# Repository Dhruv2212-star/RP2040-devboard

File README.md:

# RP2040 based devboard. 
**why did i make this board??**  
hmmmm.. well one day i realised that i have made many projects wit devboard but i have never made my own devboard.  
this was it! so this was a golden project opportunity for me to challenge myself to make something.  
i went and search some tutorials on how devboards worked and how to make them.  
Out of all of the possible devboards out there. one particular board caught my eye, it was the **RP2040** Devboard because it was reallllyy easy to make and really functional and powerful because of it's storage capacity and the no. of GPIO pins it had.  

**Now let me explain to you how i built this devboard :)**  
for a Devboard to work you need to have the basic idea of the chip architecture, with our *RP2040* chip, it uses 3.3v for the main power pins but uses 1.1v for the logic pins and fortunately for our chip it has a built in voltage control which reduces the voltage to 1.1v so no need of extra components  

**decoupling capacitors**- we are using 100nF capacitors per each power pin (IOVDD) and 1uF capacitors for VREG_IN and VREG_OUT each and 2 100nF capacitors for DVDD pin, 100nF capacitor for ADC_AVDD and 100nF for USB VDD  

**Flash storage-** for storing our code in the devboard we are using W25Q128JVS chip for this function, we are going to use QSPI pins for this connection  

**Crystal oscillator**- for this build the data sheet recommends 12Mhz crystal, and in our board we are using   
ABLS-12.000MHZ-B4-T for this  

**GPIO pin extensions**- using 1x20 connectors, we extend it to connectors where we can utilize them.  

# BOM ( Bill of materials)  
## Bill of Materials (BOM)

| Reference          | Qty | Value / Part                | Footprint                               | Purchase                                      |
| ------------------ | --: | --------------------------- | --------------------------------------- | --------------------------------------------- |
| C1, C2             |   2 | 10 µF                       | `C_0603_1608Metric`                     | [Link](https://amzn.in/d/0bsal2JG)            |
| C3, C4, C5, C9–C15 |  10 | 100 nF                      | `C_0402_1005Metric`                     | [Link](https://amzn.in/d/0h4zQ3Lf)            |
| C6, C7             |   2 | 1 µF                        | `C_0402_1005Metric`                     | [Link](https://amzn.in/d/0exjZiSL)            |
| C8                 |   1 | 100 nF                      | `C_0402_1005Metric`                     | [Link](https://amzn.in/d/0hHEodPN)            |
| C16, C17           |   2 | 27 pF                       | `C_0402_1005Metric`                     | [Link](https://amzn.in/d/0bekUa1Y)            |
| D1                 |   1 | LED                         | `LED_0603_1608Metric`                   | [Link](https://amzn.in/d/0jdhjUcx)            |
| J1                 |   1 | USB-C Receptacle USB2.0 16P | `USB_C_Receptacle_GCT_USB4105-xx-A_16P` | [Link](https://amzn.in/d/03EJbP2P)            |
| J2                 |   1 | 1×2 Pin Header              | `PinHeader_1x02_P2.54mm_Vertical`       | Cut from 1×40 header                          |
| J3                 |   1 | 1×4 Pin Header              | `PinHeader_1x04_P2.54mm_Vertical`       | Cut from 1×40 header                          |
| J4, J5             |   2 | 1×20 Pin Header             | `PinHeader_1x20_P2.54mm_Vertical`       | [Link](https://amzn.in/d/06pAoX1t)            |
| R1, R2             |   2 | 5.1 kΩ                      | `R_0603_1608Metric`                     | [Link](https://amzn.in/d/05xfBy6B)            |
| R3, R9             |   2 | 10 kΩ                       | `R_0402_1005Metric`                     | [Link](https://amzn.in/d/02u6eVpk)            |
| R4, R5             |   2 | 27.4 Ω                      | `R_0603_1608Metric`                     | [Link](https://amzn.in/d/07J2YWcO)            |
| R6, R7, R8         |   3 | 1 kΩ                        | `R_0603_1608Metric`                     | [Link](https://amzn.in/d/02u6eVpk)            |
| SW1                |   1 | RESET — TL3301AF160QG       | `SW_Push_1P1T_NO`                       | [Link](https://www.digikey.in/short/r89qvhmn) |
| U1                 |   1 | NCP1117-3.3                 | `TO-252-2`                              | [Link](https://www.digikey.in/short/ff3dmq3j) |
| U2                 |   1 | RP2040                      | `QFN-56-1EP_7x7mm`                      | [Link](https://amzn.in/d/011fsK23)            |
| U3                 |   1 | W25Q128JVS                  | `SOIC-8_5.3x5.3mm_P1.27mm`              | [Link](https://www.digikey.in/short/zzb4v2bb) |
| Y1                 |   1 | Crystal                     | `Crystal_SMD_HC49-SD`                   | [Link](https://www.digikey.in/short/9m893pn7) |

# Final schematic look: 

# PCB tracing pics on KIcad  

# Acutual PCB preview 

# 3D model view in Kicad

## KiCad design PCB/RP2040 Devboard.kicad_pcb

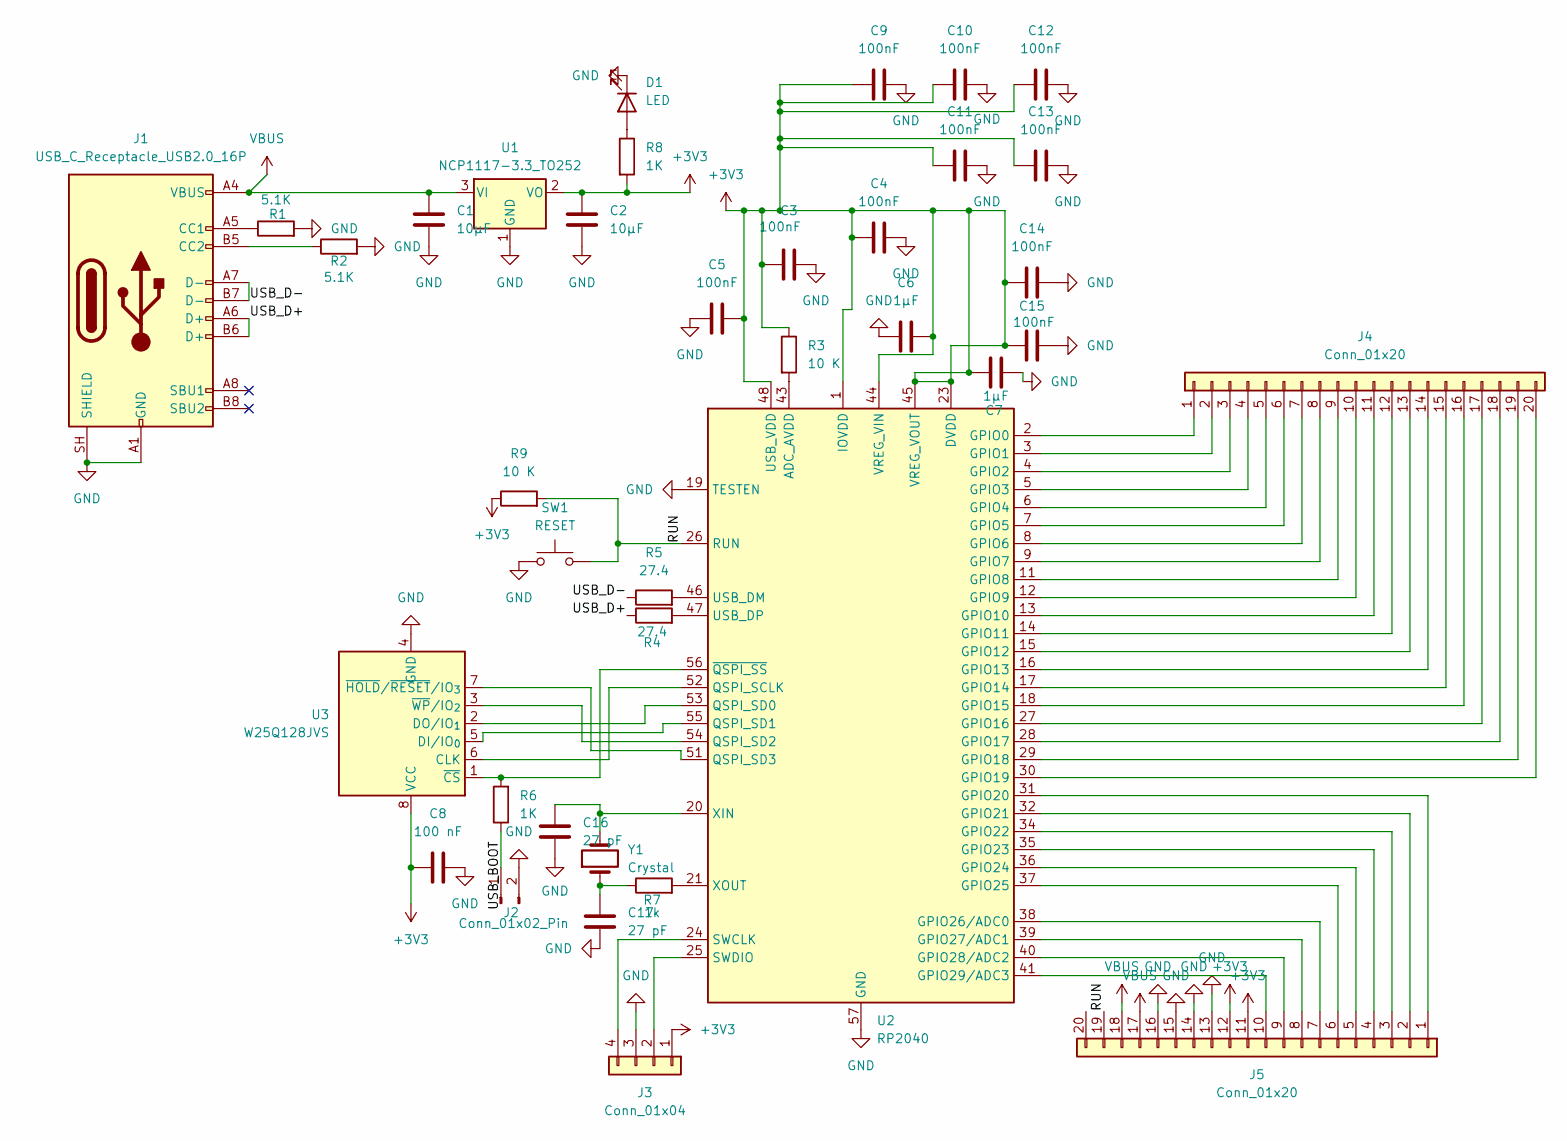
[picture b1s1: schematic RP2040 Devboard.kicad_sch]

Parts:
C1, C2: 10μF; C_0603_1608Metric
C3, C4, C5, C9, C10, C11, C12, C13, C14, C15: 100nF; C_0402_1005Metric
C6, C7: 1µF; C_0402_1005Metric
C8: 100 nF; C_0402_1005Metric
C16, C17: 27 pF; C_0402_1005Metric
D1: LED; LED_0603_1608Metric_Pad1.05x0.95mm_HandSolder
J1: USB_C_Receptacle_USB2.0_16P; USB_C_Receptacle_GCT_USB4105-xx-A_16P_TopMnt_Horizontal
J2: Conn_01x02_Pin; PinHeader_1x02_P2.54mm_Vertical
J3: Conn_01x04; PinHeader_1x04_P2.54mm_Vertical
J4, J5: Conn_01x20; PinHeader_1x20_P2.54mm_Vertical
R1, R2: 5.1K; R_0603_1608Metric
R3: 10 K; R_0402_1005Metric
R4, R5: 27.4; R_0603_1608Metric
R6, R8: 1K; R_0603_1608Metric_Pad0.98x0.95mm_HandSolder
R7: 1k; R_0603_1608Metric_Pad0.98x0.95mm_HandSolder
R9: 10 K; R_0603_1608Metric
SW1: RESET; SW_Push_1P1T_NO_E-Switch_TL3301NxxxxxG
U1: NCP1117-3.3_TO252; TO-252-2
U2: RP2040; QFN-56-1EP_7x7mm_P0.4mm_EP3.2x3.2mm
U3: W25Q128JVS; SOIC-8_5.3x5.3mm_P1.27mm
Y1: Crystal; Crystal_SMD_HC49-SD

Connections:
+3V3: C2.1, C3.1, C4.2, C5.2, C6.1, C7.2, C8.1, C9.1, C10.1, C11.1, C12.1, C13.1, C14.1, C15.1, J3.1, J5.11, J5.12, R3.1, R8.2, R9.1, U1.2 (VO), U2.1 (IOVDD), U2.10 (IOVDD), U2.22 (IOVDD), U2.23 (DVDD), U2.33 (IOVDD), U2.42 (IOVDD), U2.44 (VREG_VIN), U2.45 (VREG_VOUT), U2.48 (USB_VDD), U2.49 (IOVDD), U2.50 (DVDD), U3.8 (VCC)
/RUN: J5.19, R9.2, SW1.2, U2.26 (RUN)
/USB_BOOT: J2.1, R6.1
/USB_D+: J1.A6 (D+), J1.B6 (D+), R4.1
/USB_D-: J1.A7 (D-), J1.B7 (D-), R5.1
GND: C1.2, C2.2, C3.2, C4.1, C5.1, C6.2, C7.1, C8.2, C9.2, C10.2, C11.2, C12.2, C13.2, C14.2, C15.2, C16.2, C17.2, D1.1 (K), J1.A1 (GND), J1.A12 (GND), J1.B1 (GND), J1.B12 (GND), J1.SH (SHIELD), J2.2, J3.3, J5.13, J5.14, J5.15, J5.16, R1.2, R2.2, SW1.1, U1.1 (GND), U2.19 (TESTEN), U2.57 (GND), U3.4 (GND)
unnamed: C17.1, R7.1, Y1.1
unnamed: D1.2 (A), R8.1
unnamed: J1.A5 (CC1), R1.1
unnamed: J1.B5 (CC2), R2.1
unnamed: J3.2, U2.25 (SWDIO)
unnamed: J3.4, U2.24 (SWCLK)
unnamed: J4.1, U2.2 (GPIO0)
unnamed: J4.2, U2.3 (GPIO1)
unnamed: J4.3, U2.4 (GPIO2)
unnamed: J4.4, U2.5 (GPIO3)
unnamed: J4.5, U2.6 (GPIO4)
unnamed: J4.6, U2.7 (GPIO5)
unnamed: J4.7, U2.8 (GPIO6)
unnamed: J4.8, U2.9 (GPIO7)
unnamed: J4.9, U2.11 (GPIO8)
unnamed: J4.10, U2.12 (GPIO9)
unnamed: J4.11, U2.13 (GPIO10)
unnamed: J4.12, U2.14 (GPIO11)
unnamed: J4.13, U2.15 (GPIO12)
unnamed: J4.14, U2.16 (GPIO13)
unnamed: J4.15, U2.17 (GPIO14)
unnamed: J4.16, U2.18 (GPIO15)
unnamed: J4.17, U2.27 (GPIO16)
unnamed: J4.18, U2.28 (GPIO17)
unnamed: J4.19, U2.29 (GPIO18)
unnamed: J4.20, U2.30 (GPIO19)
unnamed: J5.1, U2.31 (GPIO20)
unnamed: J5.2, U2.32 (GPIO21)
unnamed: J5.3, U2.34 (GPIO22)
unnamed: J5.4, U2.35 (GPIO23)
unnamed: J5.5, U2.36 (GPIO24)
unnamed: J5.6, U2.37 (GPIO25)
unnamed: J5.7, U2.38 (GPIO26/ADC0)
unnamed: J5.8, U2.39 (GPIO27/ADC1)
unnamed: J5.9, U2.40 (GPIO28/ADC2)
unnamed: J5.10, U2.41 (GPIO29/ADC3)
unnamed: R3.2, U2.43 (ADC_AVDD)
unnamed: U2.52 (QSPI_SCLK), U3.6 (CLK)
unnamed: U2.53 (QSPI_SD0), U3.2 (DO/IO_{1})
unnamed: U2.55 (QSPI_SD1), U3.5 (DI/IO_{0})
unnamed: U2.54 (QSPI_SD2), U3.3 (~WP/IO_{2})
unnamed: U2.51 (QSPI_SD3), U3.7 (~HOLD/~RESET/IO_{3})
unnamed: R5.2, U2.46 (USB_DM)
unnamed: R4.2, U2.47 (USB_DP)
unnamed: C16.1, U2.20 (XIN), Y1.2
unnamed: R7.2, U2.21 (XOUT)
unnamed: R6.2, U2.56 (~QSPI_SS), U3.1 (~CS)
VBUS: C1.1, J1.A4 (VBUS), J1.A9 (VBUS), J1.B4 (VBUS), J1.B9 (VBUS), J5.17, J5.18, U1.3 (VI)

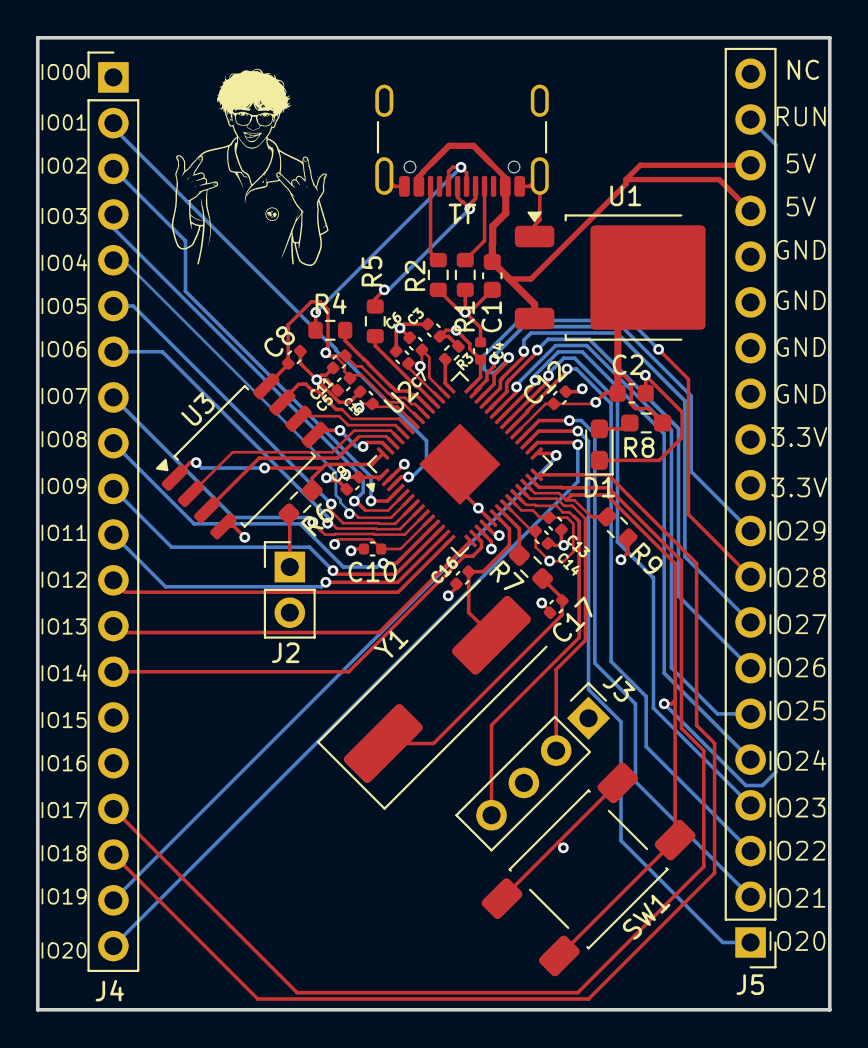
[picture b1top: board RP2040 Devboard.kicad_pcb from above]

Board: 4 copper layers, 44.0 x 54.0 mm, 37 parts (0 on the bottom side), 54 nets.

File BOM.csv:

Reference,Qty,Value,DNP,Exclude from BOM,Exclude from Board,Footprint,shopping link
"C1,C2",2,10μF,,,,Capacitor_SMD:C_0603_1608Metric,https://amzn.in/d/0bsal2JG
"C3,C4,C5,C9,C10,C11,C12,C13,C14,C15",10,100nF,,,,Capacitor_SMD:C_0402_1005Metric,https://amzn.in/d/0h4zQ3Lf
"C6,C7",2,1µF,,,,Capacitor_SMD:C_0402_1005Metric,https://amzn.in/d/0exjZiSL
C8,1,100 nF,,,,Capacitor_SMD:C_0402_1005Metric,https://amzn.in/d/0hHEodPN
"C16,C17",2,27 pF,,,,Capacitor_SMD:C_0402_1005Metric,https://amzn.in/d/0bekUa1Y
D1,1,LED,,,,LED_SMD:LED_0603_1608Metric_Pad1.05x0.95mm_HandSolder,https://amzn.in/d/0jdhjUcx
J1,1,USB_C_Receptacle_USB2.0_16P,,,,Connector_USB:USB_C_Receptacle_GCT_USB4105-xx-A_16P_TopMnt_Horizontal,https://amzn.in/d/03EJbP2P
J2,1,Conn_01x02_Pin,,,,Connector_PinHeader_2.54mm:PinHeader_1x02_P2.54mm_Vertical,cut a piece from 1x40 below
J3,1,Conn_01x04,,,,Connector_PinHeader_2.54mm:PinHeader_1x04_P2.54mm_Vertical,cut a piece from 1x40 below
"J4,J5",2,Conn_01x20,,,,Connector_PinHeader_2.54mm:PinHeader_1x20_P2.54mm_Vertical,https://amzn.in/d/06pAoX1t
"R1,R2",2,5.1K,,,,Resistor_SMD:R_0603_1608Metric,https://amzn.in/d/05xfBy6B
"R3,R9",2,10 K,,,,Resistor_SMD:R_0402_1005Metric,https://amzn.in/d/02u6eVpk
"R4,R5",2,27.4,,,,Resistor_SMD:R_0603_1608Metric,https://amzn.in/d/07J2YWcO
"R6,R7,R8",3,1K,,,,Resistor_SMD:R_0603_1608Metric_Pad0.98x0.95mm_HandSolder,https://amzn.in/d/02u6eVpk
SW1,1,"RESET, TL3301AF160QG",,,,Button_Switch_SMD:SW_Push_1P1T_NO_E-Switch_TL3301NxxxxxG,https://www.digikey.in/short/r89qvhmn
U1,1,NCP1117-3.3_TO252,,,,Package_TO_SOT_SMD:TO-252-2,https://www.digikey.in/short/ff3dmq3j
U2,1,RP2040,,,,Package_DFN_QFN:QFN-56-1EP_7x7mm_P0.4mm_EP3.2x3.2mm,https://amzn.in/d/011fsK23
U3,1,W25Q128JVS,,,,Package_SO:SOIC-8_5.3x5.3mm_P1.27mm,https://www.digikey.in/short/zzb4v2bb
Y1,1,Crystal,,,,Crystal:Crystal_SMD_HC49-SD,https://www.digikey.in/short/9m893pn7
